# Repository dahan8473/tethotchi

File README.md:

# Tethotchi

A virtual pet keychain shaped like a tiny CRT TV. Made by [Tethos](https://tethos.ca) / Tech for Social Impact as merch: you feed it, it grows, it visits other Tethotchis over Bluetooth, and it dies if you forget about it.

<sub>Product render generated from the CAD in this repo (GPT Image 2). Real units are still being built.</sub>

## Specs

| | |
|---|---|
| Size | 52 x 42 x 18.4 mm, plus antennas and ball-chain loop |
| Screen | 1.7" 128x64 monochrome FSTN (ST7567) |
| Brain + radio | u-blox ANNA-B112 (nRF52832, certified BLE module with built-in antenna) |
| Power | CR2477 coin cell behind a twist-lock cap, 6-12 month target |
| Input / output | 4 side buttons, magnetic buzzer |
| Talks to | other Tethotchis (pet visits), event beacons, a web page (sync + firmware updates over Web Bluetooth) |
| Cost | ~$19-23 per unit at 100 units |

## What's in here

```
hardware/
  layout.py, circuit.py     single source of truth: placement, dimensions, every pin's net
  pcb/                      KiCad 10 board, generated by script; JLC fab files in pcb/fab/
  shell/                    build123d CAD for the case; STEP/STL in shell/out/
  art/                      silkscreen art generator (Plex Mono, Tethos mark, pixel TV)
  renders/                  board, shell and fit-check renders
  parts.md                  BOM with LCSC numbers and costs
  ORDER.md                  what to order where for the first 5
firmware/                   Zephyr / nRF Connect SDK (early scaffold)
web/                        Web Bluetooth updater (vendored mcumgr-web)
```

The board and the case are both code. Change `layout.py`, rerun the pipeline in [hardware/README.md](hardware/README.md), and the PCB, shell, collision check and factory files all follow.

## Board

4 layers, 48.4 x 38.4 mm, 0.8 mm thick, assembled by JLCPCB. The screen side carries the art; the battery side carries everything else.

| Screen side | Battery side |
|---|---|
|  |  |

## Case

Two halves that close with two M1.7 screws, a twist-lock battery cap (printed in three tolerances to pick the best fit), and button plungers printed on a sprue. The first run of five has numbered backs, ★ 1/5 to ★ 5/5.

## Status

- [x] Hardware spec, BOM, shell v0.1, PCB routed (KiCad DRC clean), fab files
- [ ] First 5 units ordered and assembled
- [ ] Firmware: pet loop, BLE visits, web sync, OTA
- [ ] 100-unit run

Not affiliated with Bandai. Tamagotchi is their trademark; this is a fan homage with its own body, mascot and code.

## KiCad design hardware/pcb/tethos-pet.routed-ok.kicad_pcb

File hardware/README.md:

# Tethotchi hardware

Everything is generated from two files:
- `layout.py`: board outline, part positions, shell dimensions, antenna keep-out
- `circuit.py`: parts, LCSC numbers, footprints, every pin's net

## Pipeline

```sh
# 1. floor plan + collision check
.venv/bin/python hardware/plan_view.py

# 2. PCB (KiCad 10, its bundled Python)
KPY=~/Applications/KiCad/KiCad.app/Contents/Frameworks/Python.framework/Versions/3.9/bin/python3
$KPY hardware/pcb/build_pcb.py          # outline, placement, nets, planes, antenna keep-out
PASSES=150 $KPY hardware/pcb/route.py   # power fanout + Freerouting (needs Java 25+) + ground pours
.venv/bin/python hardware/art/make_art.py   # silkscreen art -> art/art.json
$KPY hardware/pcb/add_art.py                # stamp it on the routed board
~/Applications/KiCad/KiCad.app/Contents/MacOS/kicad-cli pcb drc --severity-error hardware/pcb/tethos-pet.kicad_pcb

# 3. factory files -> hardware/pcb/fab/{gerbers.zip,bom.csv,cpl.csv}
.venv/bin/python hardware/pcb/export_fab.py

# 4. shell (build123d) -> hardware/shell/out/*.step|stl, fit check against the board parts
.venv/bin/python hardware/shell/shell.py
.venv/bin/python hardware/shell/fit_check.py
```

Freerouting isn't deterministic. `pcb/tethos-pet.routed-ok.kicad_pcb` is a run that passed DRC with 0 errors / 0 unconnected.

## Board
- 48.4 x 38.4 mm, 4 layers, 0.8 mm, ENIG (the CR2477 (-) contact is a bare pad)
- L1 front (LCD side): J1 + LCD caps. L2 GND plane. L3 VBAT plane. L4 back: everything else
- Vias 0.45/0.3 mm, tented (JLC's no-fee via size). Min track/space 0.09 mm (SWD escape from the module only)
- u-blox ANNA-B112 on the top edge per SIM appendix B.2 (edge version): package 1.55 mm from the edge,
  copper keep-out on all layers, ANT_GND1 strip to the edge

## Shell
- `shell/out/front.step`, `back.step`, `cap_15/25/35.step` (twist-cap fit variants), `button.step` (x4)
- First run of 5: `back_1of5.step` .. `back_5of5.step`, star + edition number debossed beside the cap
- Fasteners: 2x M1.7 x 10 self-tapping, from the back

## Before ordering
- [ ] JLC's assembly preview: check part rotations (SOT-23, crystal, connector are the usual offenders)
- [ ] Email u-blox support for the ANNA-B112 B.2 reference Gerbers and compare the antenna area
- [ ] First run is 5 units: U1 comes from JLC stock (`RUN_QTY` in export_fab.py), order 5 LCDs from BuyDisplay

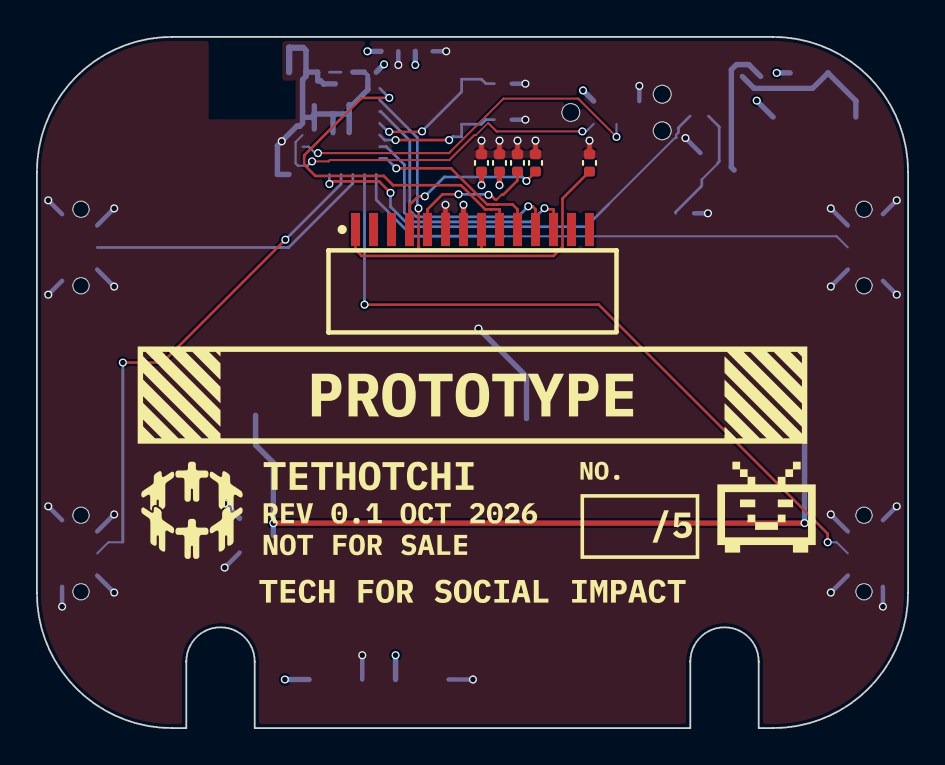
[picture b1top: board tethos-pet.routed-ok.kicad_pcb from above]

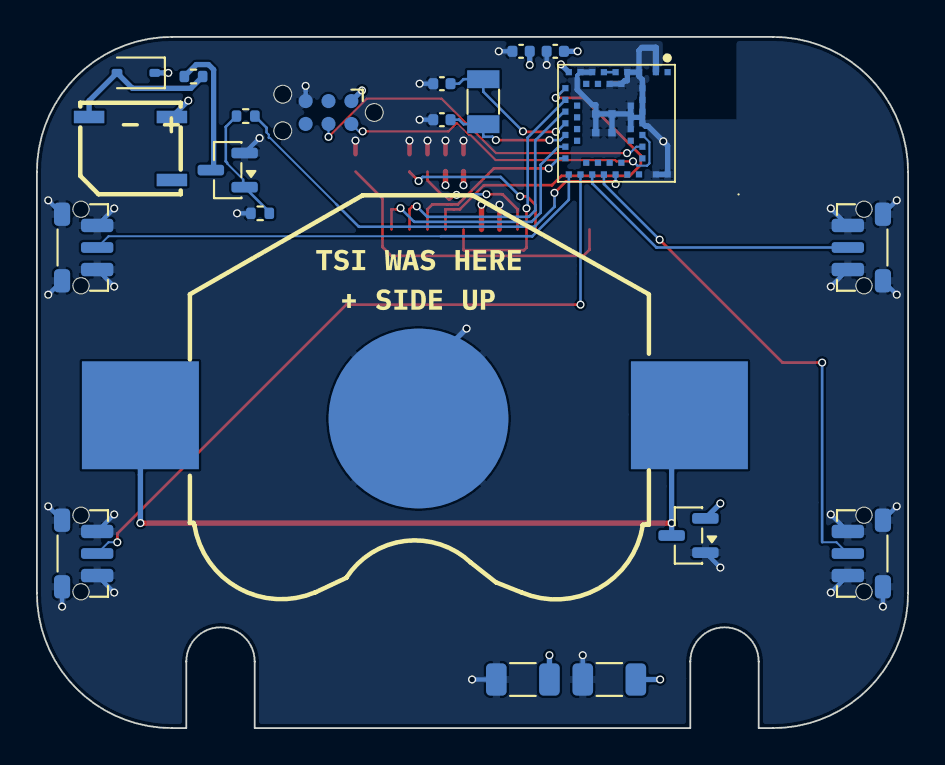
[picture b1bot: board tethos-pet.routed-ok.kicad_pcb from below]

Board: 4 copper layers, 48.4 x 38.4 mm, 27 parts (21 on the bottom side), 24 nets.

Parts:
BT1: CR2477 clip MY-2477-02; BAT-SMD_MY-2477-02
BZ1: MLT-5020; BUZ-SMD_L5.0-W5.5-P4.60
C1, C2: 100uF 6.3V X5R 1206; C_1206_3216Metric
C3: 4.7uF 10V X5R 0402; C_0402_1005Metric
C4, C11: 100nF 16V X7R 0402; C_0402_1005Metric
C5, C6: 20pF C0G 0402; C_0402_1005Metric
C7, C8, C9, C10: 1uF 25V X5R 0402; C_0402_1005Metric
D1: 1N4148WS; D_SOD-323
J1: 1.0-B-14PWB; FPC-SMD_14P-P1.00_HDGC_1.0-B-14PWB
Q1: 2N7002; SOT-23
Q2: AO3401A; SOT-23
R1: 47R 0402; R_0402_1005Metric
R2: 100R 0402; R_0402_1005Metric
R3: 100k 0402; R_0402_1005Metric
SW1, SW2, SW3, SW4: SKRTLAE010; SW_Push_1P1T-MP_NO_Horizontal_Alps_SKRTLAE010
TP1: TC2030-NL; Tag-Connect_TC2030-IDC-NL_2x03_P1.27mm_Vertical
U1: ANNA-B112; BULETM-SMD_ANNA-B112
Y1: 32.768kHz 12.5pF 3215; Crystal_SMD_3215-2Pin_3.2x1.5mm

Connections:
ANT_FEED: U1.5, U1.6
BTN_A: SW1.2, U1.27
BTN_B: SW2.2, U1.28
BTN_C: SW3.2, U1.25
BTN_D: SW4.2, U1.26
BUZZ: R2.1, U1.29
BUZZ_G: Q1.1, R2.2, R3.1
BZ_D: Q1.3, R1.2
BZ_R: BZ1.2, D1.2, R1.1
GND: BT1.3, C1.2, C2.2, C3.2, C4.2, C5.2, C6.2, C7.2, C8.2, C9.2, C10.2, C11.2, J1.6, Q1.2, Q2.1, R3.2, SW1.1, SW1.MP, SW2.1, SW2.MP, SW3.1, SW3.MP, SW4.1, SW4.MP, TP1.5, U1.2, U1.3, U1.4, U1.7, U1.8, U1.10, U1.11, U1.32, U1.33, U1.41, U1.42, U1.43, U1.44, U1.46, U1.47, U1.48, U1.49, U1.50, U1.51, U1.52
LCD_A0: J1.10, U1.20
LCD_CS: J1.12, U1.19
LCD_RST: J1.11, U1.16
LCD_SCL: J1.9, U1.14
LCD_SDA: J1.8, U1.15
LCD_V0: C7.1, J1.5
LCD_VG: C9.1, J1.1
LCD_XV0: C8.1, J1.4
SWDCLK: TP1.4, U1.39
SWDIO: TP1.2, U1.40
VBAT: BZ1.1, C1.1, C2.1, C3.1, C4.1, C10.1, C11.1, D1.1, J1.7, Q2.2, TP1.1, U1.9
VCELL: BT1.1, BT1.2, Q2.3
XL1: C5.1, U1.17, Y1.1
XL2: C6.1, U1.18, Y1.2

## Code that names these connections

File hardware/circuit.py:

"""Circuit netlist: single source of truth for the schematic, PCB nets and BOM.

Every pin decision cites the datasheet it came from (hardware/datasheets/).
Run: .venv/bin/python hardware/circuit.py   -> prints BOM + per-net connections, checks for typos.
"""

# ref: (value, LCSC, footprint, {pin: net})
PARTS = {
    # --- Power: CR2477 -> reverse-polarity P-FET -> VBAT ---
    "BT1": ("CR2477 clip MY-2477-02", "C2979175", "tethos:BAT-SMD_MY-2477-02",
            {"1": "VCELL", "2": "VCELL", "3": "GND"}),   # 1,2 = clip tabs (+); 3 = bare ENIG pad under the cell (-)
    "Q2": ("AO3401A", "C15127", "Package_TO_SOT_SMD:SOT-23",
           # KiCad SOT-23 pins: 1 G, 2 S, 3 D. Drain to cell, source to load, gate to GND
           {"3": "VCELL", "2": "VBAT", "1": "GND"}),
    "C1": ("100uF 6.3V X5R 1206", "C380356", "Capacitor_SMD:C_1206_3216Metric", {"1": "VBAT", "2": "GND"}),
    "C2": ("100uF 6.3V X5R 1206", "C380356", "Capacitor_SMD:C_1206_3216Metric", {"1": "VBAT", "2": "GND"}),

    # --- MCU: u-blox ANNA-B112 (nRF52832). Pin numbers: ANNA-B112 datasheet table 7 ---
    "U1": ("ANNA-B112", "C33688798", "tethos:BULETM-SMD_ANNA-B112", {
        "1": None,           # ANT_PCB: corner version only
        "2": "GND", "3": "GND",             # ANT_GND1/2: grounded for the edge version (SIM B.2)
        "5": "ANT_FEED", "6": "ANT_FEED",   # ANT_INT tied to ANT: use the internal antenna
        "9": "VBAT",
        # Signals only on the outer pad ring so they escape without vias under the module.
        # Bottom row (14-20) and right column (25-31); pin numbers from datasheet table 7.
        "14": "LCD_SCL",     # P0.15
        "15": "LCD_SDA",     # P0.16
        "16": "LCD_RST",     # P0.18
        "19": "LCD_CS",      # P0.03
        "20": "LCD_A0",      # P0.02
        "25": "BTN_C",       # P0.31 (low-drive pin, fine for an input)
        "26": "BTN_D",       # P0.30
        "27": "BTN_A",       # P0.29
        "28": "BTN_B",       # P0.28
        "29": "BUZZ",        # P0.27, 4 kHz PWM counts as low frequency for this pin
        "17": "XL1", "18": "XL2",           # P0.00 / P0.01 LFXO
        "39": "SWDCLK", "40": "SWDIO",      # inner row: the only pins that need vias under the module
        **{str(p): "GND" for p in (4, 7, 8, 10, 11, 32, 33, 41, 42, 43, 44, 46, 47, 48, 49, 50, 51, 52)},
    }),
    "C3": ("4.7uF 10V X5R 0402", "C23733", "Capacitor_SMD:C_0402_1005Metric", {"1": "VBAT", "2": "GND"}),
    "C4": ("100nF 16V X7R 0402", "C1525", "Capacitor_SMD:C_0402_1005Metric", {"1": "VBAT", "2": "GND"}),

    # 32.768 kHz crystal, CL 12.5 pF -> C = 2*CL - (C_pin + C_pcb) ~ 25 - 5 = 20 pF
    "Y1": ("32.768kHz 12.5pF 3215", "C32346", "Crystal:Crystal_SMD_3215-2Pin_3.2x1.5mm", {"1": "XL1", "2": "XL2"}),
    "C5": ("20pF C0G 0402", "C1554", "Capacitor_SMD:C_0402_1005Metric", {"1": "XL1", "2": "GND"}),
    "C6": ("20pF C0G 0402", "C1554", "Capacitor_SMD:C_0402_1005Metric", {"1": "XL2", "2": "GND"}),

    # --- LCD: ERC12864FSF-9 via 14-pin 1.0 mm FPC. Pinout: ERC12864-9 datasheet section 4.1 ---
    # The ribbon folds 180 deg behind the LCD: LCD pin 1 (right edge, seen from the front) lands on pad 14.
    # Dual-contact connector, so it works whichever face the ribbon's contacts end up on.
    "J1": ("1.0-B-14PWB", "C2915494", "tethos:FPC-SMD_14P-P1.00_HDGC_1.0-B-14PWB", {
        "1": "LCD_VG",  # LCD pin 14 VG
        "2": None,  # LCD pin 13 NC
        "3": None,  # LCD pin 12 NC
        "4": "LCD_XV0",  # LCD pin 11 XV0
        "5": "LCD_V0",  # LCD pin 10 V0
        "6": "GND",  # LCD pin 9 VSS
        "7": "VBAT",  # LCD pin 8 VDD
        "8": "LCD_SDA",  # LCD pin 7 SDA
        "9": "LCD_SCL",  # LCD pin 6 SCL
        "10": "LCD_A0",  # LCD pin 5 A0
        "11": "LCD_RST",  # LCD pin 4 RST
        "12": "LCD_CS",  # LCD pin 3 CS
        "13": None,  # LCD pin 2 BLK
        "14": None,  # LCD pin 1 BLA
    }),
    "C7": ("1uF 25V X5R 0402", "C52923", "Capacitor_SMD:C_0402_1005Metric", {"1": "LCD_V0", "2": "GND"}),
    "C8": ("1uF 25V X5R 0402", "C52923", "Capacitor_SMD:C_0402_1005Metric", {"1": "LCD_XV0", "2": "GND"}),
    "C9": ("1uF 25V X5R 0402", "C52923", "Capacitor_SMD:C_0402_1005Metric", {"1": "LCD_VG", "2": "GND"}),
    "C10": ("1uF 25V X5R 0402", "C52923", "Capacitor_SMD:C_0402_1005Metric", {"1": "VBAT", "2": "GND"}),
    "C11": ("100nF 16V X7R 0402", "C1525", "Capacitor_SMD:C_0402_1005Metric", {"1": "VBAT", "2": "GND"}),

    # --- Buttons: Alps SKRTLAE010. Datasheet p.3: pins 1 and 3 are joined, the switch is between them and 2 ---
    # Inputs use the nRF internal pull-ups; pressing shorts the input to GND.
    "SW1": ("SKRTLAE010", "C110293", "Button_Switch_SMD:SW_Push_1P1T-MP_NO_Horizontal_Alps_SKRTLAE010", {"1": "GND", "2": "BTN_A", "MP": "GND"}),
    "SW2": ("SKRTLAE010", "C110293", "Button_Switch_SMD:SW_Push_1P1T-MP_NO_Horizontal_Alps_SKRTLAE010", {"1": "GND", "2": "BTN_B", "MP": "GND"}),
    "SW3": ("SKRTLAE010", "C110293", "Button_Switch_SMD:SW_Push_1P1T-MP_NO_Horizontal_Alps_SKRTLAE010", {"1": "GND", "2": "BTN_C", "MP": "GND"}),
    "SW4": ("SKRTLAE010", "C110293", "Button_Switch_SMD:SW_Push_1P1T-MP_NO_Horizontal_Alps_SKRTLAE010", {"1": "GND", "2": "BTN_D", "MP": "GND"}),

    # --- Buzzer: MLT-5020 magnetic, low-side N-FET, flyback diode, series R limits coin-cell surge ---
    "BZ1": ("MLT-5020", "C94598", "tethos:BUZ-SMD_L5.0-W5.5-P4.60", {"1": "VBAT", "2": "BZ_R", "3": None}),
    # coil is 12 ohm: 47 ohm series keeps the peak near 50 mA
    "R1": ("47R 0402", "C25118", "Resistor_SMD:R_0402_1005Metric", {"1": "BZ_R", "2": "BZ_D"}),
    "D1": ("1N4148WS", "C2128", "Diode_SMD:D_SOD-323", {"1": "VBAT", "2": "BZ_R"}),
    "Q1": ("2N7002", "C8545", "Package_TO_SOT_SMD:SOT-23", {"3": "BZ_D", "2": "GND", "1": "BUZZ_G"}),
    "R2": ("100R 0402", "C25076", "Resistor_SMD:R_0402_1005Metric", {"1": "BUZZ", "2": "BUZZ_G"}),
    "R3": ("100k 0402", "C25741", "Resistor_SMD:R_0402_1005Metric", {"1": "BUZZ_G", "2": "GND"}),

    # --- Programming: Tag-Connect TC2030-NL (nRF52 DK debug out) ---
    "TP1": ("TC2030-NL", "", "Connector:Tag-Connect_TC2030-IDC-NL_2x03_P1.27mm_Vertical", {
        "1": "VBAT", "2": "SWDIO", "3": None, "4": "SWDCLK", "5": "GND", "6": None}),   # SWD needs no reset/trace
}

# Things to confirm from datasheets before layout (kept here so they can't be forgotten)
OPEN = [
    "SKRTLAE010 footprint: 2x 0.9 mm guide holes, no copper under the actuator (datasheet p.3 hatched area).",
    "J1 is friction-fit (no latch): check the folded ribbon stays seated when the shell closes.",
    "ANNA-B112 edge layout follows SIM appendix B.2 from the figures; ask u-blox support for the reference Gerbers to confirm before production.",
    "LCD VDD min is 2.8 V; CR2477 sags below that near end of life. Measure contrast at 2.6-2.8 V on the prototype.",
]


def nets():
    out = {}
    for ref, (_, _, _, pins) in PARTS.items():
        for pin, net in pins.items():
            if net:
                out.setdefault(net, []).append(f"{ref}.{pin}")
    return out


def check():
    problems = []
    for net, conns in nets().items():
        if len(conns) < 2:
            problems.append(f"net {net} has one connection: {conns}")
    return problems


if __name__ == "__main__":
    for net, conns in sorted(nets().items()):
        print(f"{net:10s} {', '.join(conns)}")
    print()
    probs = check()
    print("\n".join(probs) if probs else "every net has 2+ connections")
    print("\nOpen items:\n- " + "\n- ".join(OPEN))
